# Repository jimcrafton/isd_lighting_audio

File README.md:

# isd_lighting_audio

Arduino nano code to control the audio and lighting effects for a Zvesda 1/2700 Star Destroyer model.

For WIP pictures of the model, see:
https://photos.app.goo.gl/XD3XtKHCLR6KuFhS9

Lighting effects based on NeoPixels, and custom code I wrote to activate them individually.

[Star Destroyer Start up Video, still WIP](https://photos.google.com/share/AF1QipOuW4K0J_yMDQOA_agWgGm0RNDhcW0MBYs12XNCtcLftvfbEZarzZgI_aQ6eU1jtA/photo/AF1QipNUU_HIZ2aDgCDPC5ougGlNus44bEYMES7hw9cd?key=Q3RFTWRxT3RHVC1FSkhQc0VzXzNoM1VPVWRwSmZR)

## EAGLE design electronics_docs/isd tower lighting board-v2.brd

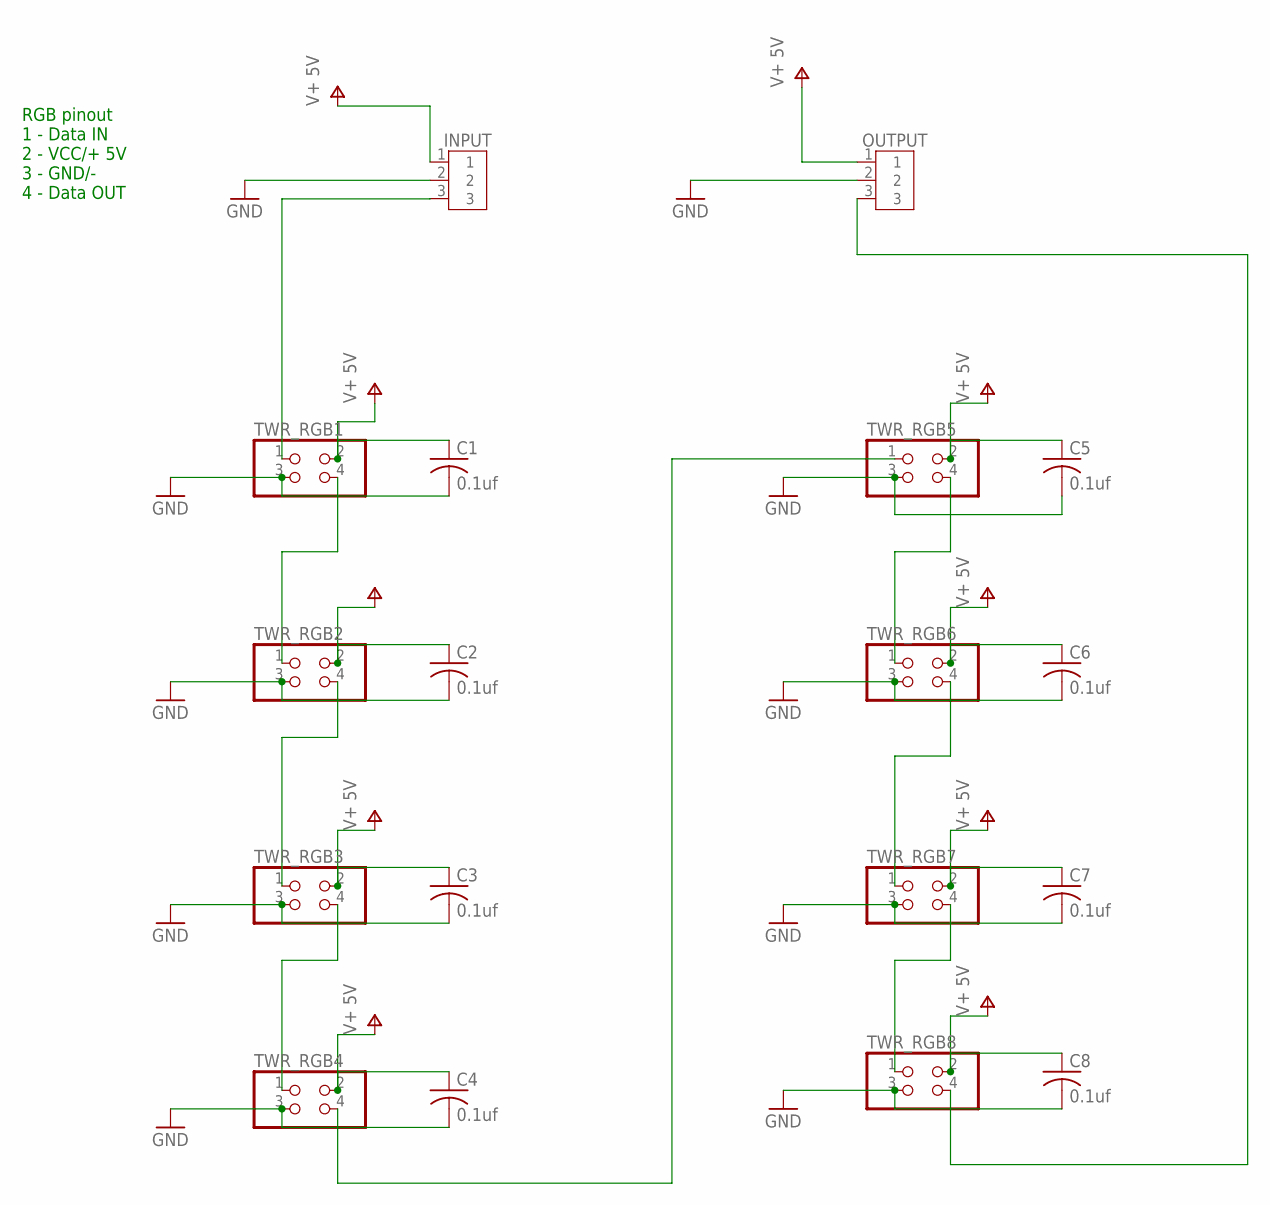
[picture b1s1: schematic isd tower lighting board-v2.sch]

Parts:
C1, C2, C3, C4, C5, C6, C7, C8: 0.1uf; C0805
INPUT: B3B-XH-A
OUTPUT: B3B-XH-A
TWR_RGB1, TWR_RGB2, TWR_RGB3, TWR_RGB4, TWR_RGB5, TWR_RGB6, TWR_RGB7, TWR_RGB8: PINHD-2X2; 2X02

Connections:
GND: C1.2, C2.2, C3.2, C4.2, C5.2, C6.2, C7.2, C8.2, INPUT.2, OUTPUT.2, TWR_RGB1.3, TWR_RGB2.3, TWR_RGB3.3, TWR_RGB4.3, TWR_RGB5.3, TWR_RGB6.3, TWR_RGB7.3, TWR_RGB8.3
unnamed: INPUT.3, TWR_RGB1.1
unnamed: TWR_RGB5.4, TWR_RGB6.1
unnamed: TWR_RGB6.4, TWR_RGB7.1
unnamed: TWR_RGB7.4, TWR_RGB8.1
unnamed: TWR_RGB4.4, TWR_RGB5.1
unnamed: TWR_RGB3.4, TWR_RGB4.1
unnamed: TWR_RGB2.4, TWR_RGB3.1
unnamed: TWR_RGB1.4, TWR_RGB2.1
unnamed: OUTPUT.3, TWR_RGB8.4
V+: C1.1, C2.1, C3.1, C4.1, C5.1, C6.1, C7.1, C8.1, INPUT.1, OUTPUT.1, TWR_RGB1.2, TWR_RGB2.2, TWR_RGB3.2, TWR_RGB4.2, TWR_RGB5.2, TWR_RGB6.2, TWR_RGB7.2, TWR_RGB8.2

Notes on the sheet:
RGB pinout 1 - Data IN 2 - VCC/+ 5V 3 - GND/- 4 - Data OUT

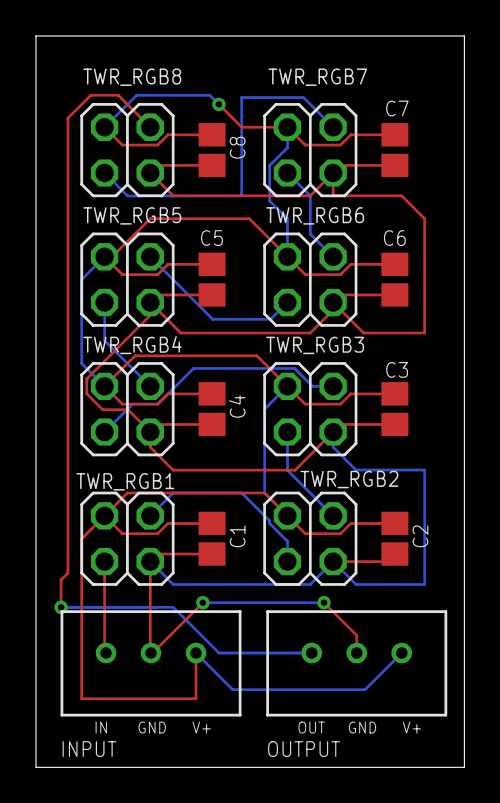
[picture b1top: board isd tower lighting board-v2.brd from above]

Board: 2 copper layers, 23.8 x 40.6 mm, 18 parts (0 on the bottom side), 11 nets.

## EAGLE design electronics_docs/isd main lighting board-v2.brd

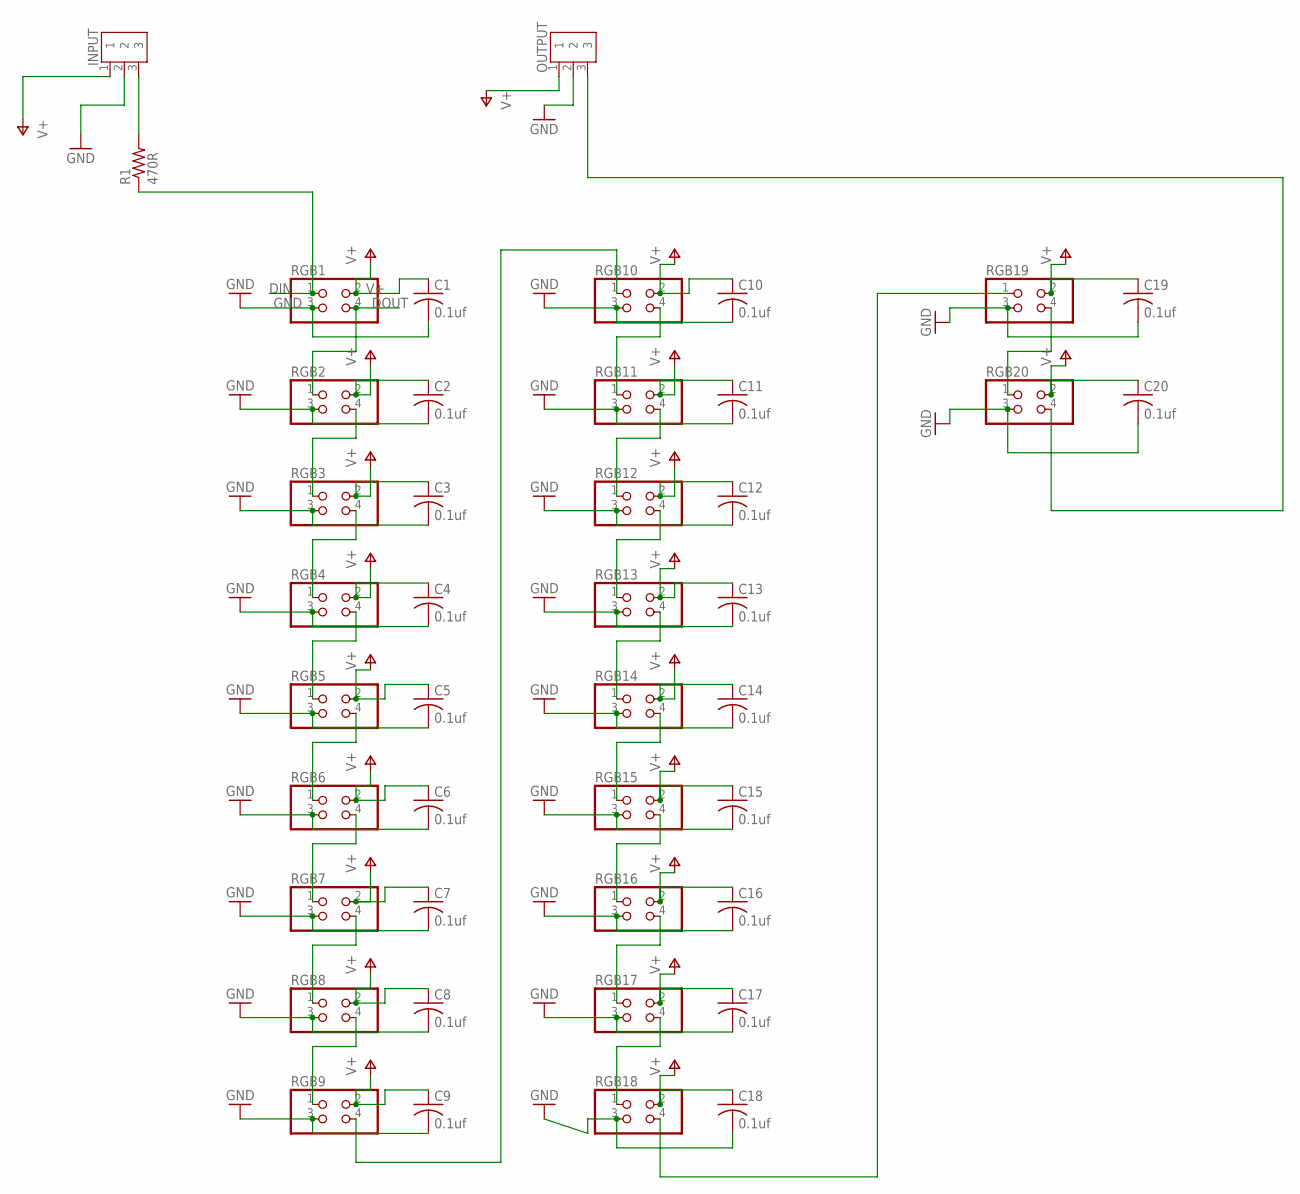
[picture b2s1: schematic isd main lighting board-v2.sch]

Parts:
C1, C2, C3, C4, C5, C6, C7, C8, C9, C10, C11, C12, C13, C14, C15, C16, C17, C18, C19, C20: 0.1uf; C0805
INPUT: B3B-XH-A
OUTPUT: B3B-XH-A
R1: 470R; 0204/5
RGB1, RGB2, RGB3, RGB4, RGB5, RGB6, RGB7, RGB8, RGB9, RGB10, RGB11, RGB12, RGB13, RGB14, RGB15, RGB16, RGB17, RGB18, RGB19, RGB20: PINHD-2X2; 2X02

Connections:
DIN: R1.1, RGB1.1
DOUT: RGB1.4, RGB2.1
GND: C1.2, C2.2, C3.2, C4.2, C5.2, C6.2, C7.2, C8.2, C9.2, C10.2, C11.2, C12.2, C13.2, C14.2, C15.2, C16.2, C17.2, C18.2, C19.2, C20.2, INPUT.2, OUTPUT.2, RGB1.3, RGB2.3, RGB3.3, RGB4.3, RGB5.3, RGB6.3, RGB7.3, RGB8.3, RGB9.3, RGB10.3, RGB11.3, RGB12.3, RGB13.3, RGB14.3, RGB15.3, RGB16.3, RGB17.3, RGB18.3, RGB19.3, RGB20.3
unnamed: INPUT.3, R1.2
unnamed: OUTPUT.3, RGB20.4
unnamed: RGB18.4, RGB19.1
unnamed: RGB8.4, RGB9.1
unnamed: RGB16.4, RGB17.1
unnamed: RGB19.4, RGB20.1
unnamed: RGB15.4, RGB16.1
unnamed: RGB14.4, RGB15.1
unnamed: RGB17.4, RGB18.1
unnamed: RGB13.4, RGB14.1
unnamed: RGB12.4, RGB13.1
unnamed: RGB11.4, RGB12.1
unnamed: RGB10.4, RGB11.1
unnamed: RGB9.4, RGB10.1
unnamed: RGB7.4, RGB8.1
unnamed: RGB6.4, RGB7.1
unnamed: RGB5.4, RGB6.1
unnamed: RGB4.4, RGB5.1
unnamed: RGB3.4, RGB4.1
unnamed: RGB2.4, RGB3.1
V+: C1.1, C2.1, C3.1, C4.1, C5.1, C6.1, C7.1, C8.1, C9.1, C10.1, C11.1, C12.1, C13.1, C14.1, C15.1, C16.1, C17.1, C18.1, C19.1, C20.1, INPUT.1, OUTPUT.1, RGB1.2, RGB2.2, RGB3.2, RGB4.2, RGB5.2, RGB6.2, RGB7.2, RGB8.2, RGB9.2, RGB10.2, RGB11.2, RGB12.2, RGB13.2, RGB14.2, RGB15.2, RGB16.2, RGB17.2, RGB18.2, RGB19.2, RGB20.2

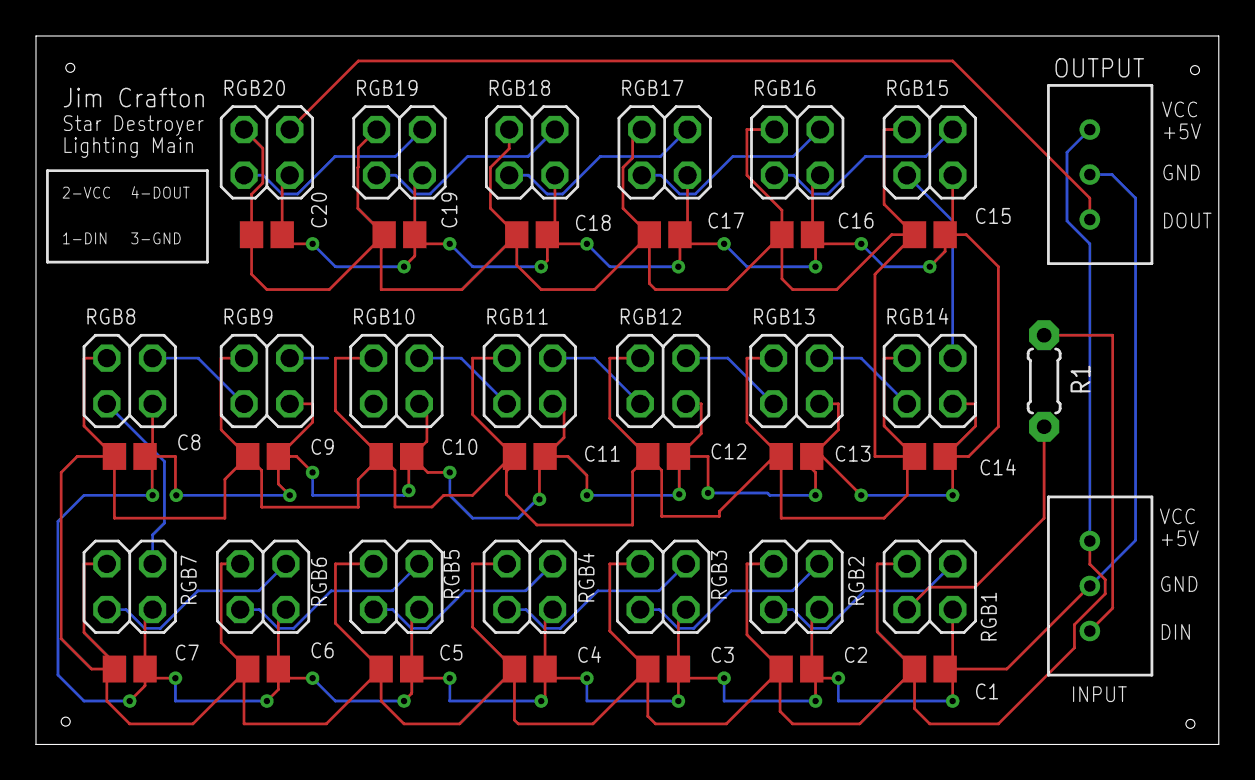
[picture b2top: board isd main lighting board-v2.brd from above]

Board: 2 copper layers, 65.7 x 39.4 mm, 43 parts (0 on the bottom side), 24 nets.

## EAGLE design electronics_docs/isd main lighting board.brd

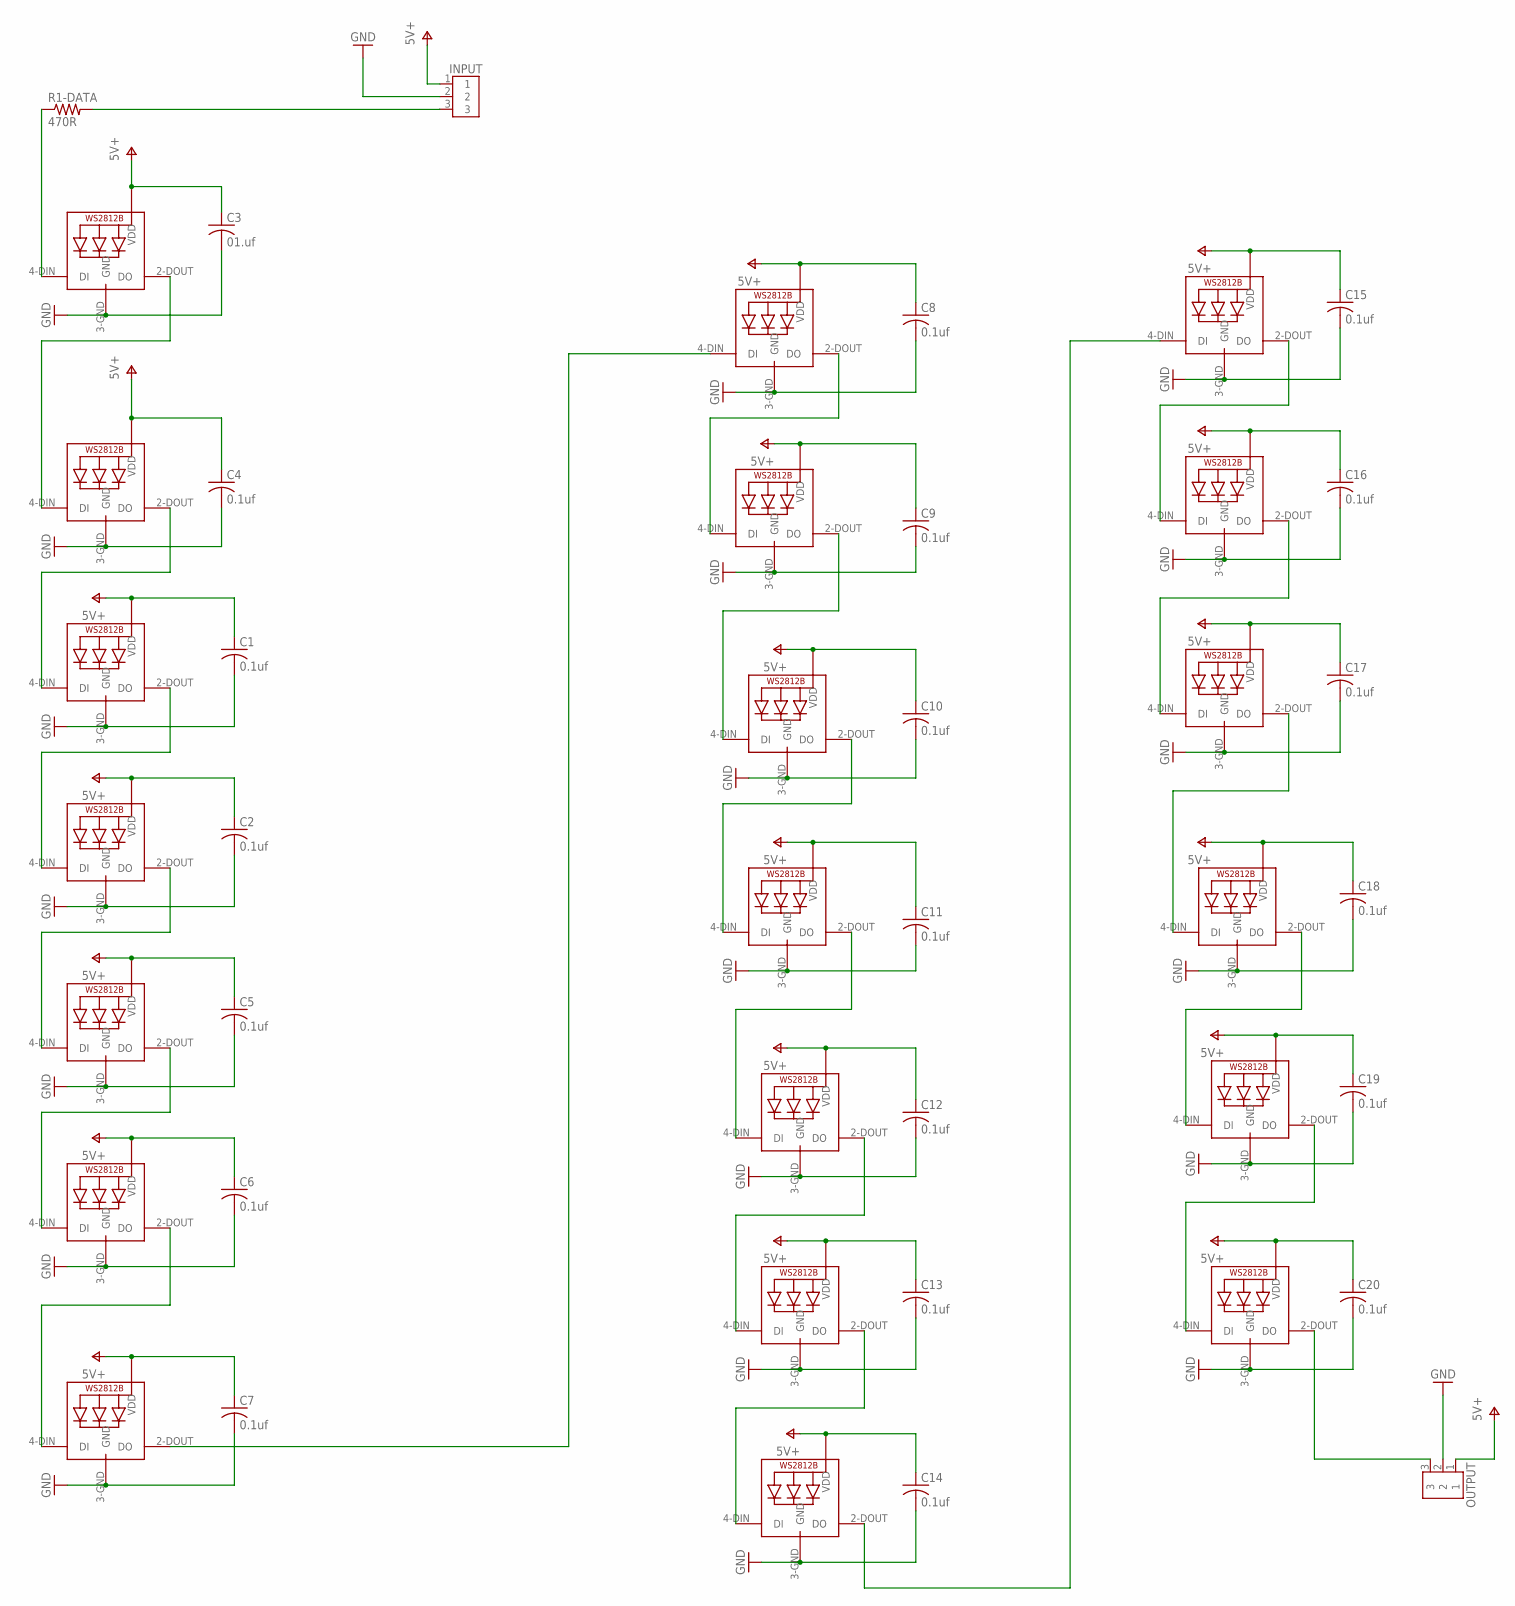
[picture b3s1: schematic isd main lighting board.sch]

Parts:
C1, C2, C4, C5, C6, C7, C8, C9, C10, C11, C12, C13, C14, C15, C16, C17, C18, C19, C20: 0.1uf; C0805K
C3: 01.uf; C0805K
INPUT: B3B-XH-A
OUTPUT: B3B-XH-A
R1-DATA: 470R; 0204/5
RGB1, RGB2, RGB3, RGB4, RGB5, RGB6, RGB7, RGB8, RGB9, RGB10, RGB11, RGB12, RGB13, RGB14, RGB15, RGB16, RGB17, RGB18, RGB19, RGB20: WS2812B_5050N; WS2812B-NARROW

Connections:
GND: C1.2, C2.2, C3.2, C4.2, C5.2, C6.2, C7.2, C8.2, C9.2, C10.2, C11.2, C12.2, C13.2, C14.2, C15.2, C16.2, C17.2, C18.2, C19.2, C20.2, INPUT.2, OUTPUT.2, RGB1.3-GND (GND), RGB2.3-GND (GND), RGB3.3-GND (GND), RGB4.3-GND (GND), RGB5.3-GND (GND), RGB6.3-GND (GND), RGB7.3-GND (GND), RGB8.3-GND (GND), RGB9.3-GND (GND), RGB10.3-GND (GND), RGB11.3-GND (GND), RGB12.3-GND (GND), RGB13.3-GND (GND), RGB14.3-GND (GND), RGB15.3-GND (GND), RGB16.3-GND (GND), RGB17.3-GND (GND), RGB18.3-GND (GND), RGB19.3-GND (GND), RGB20.3-GND (GND)
unnamed: R1-DATA.1, RGB1.4-DIN (DI)
unnamed: RGB1.2-DOUT (DO), RGB2.4-DIN (DI)
unnamed: RGB2.2-DOUT (DO), RGB3.4-DIN (DI)
unnamed: INPUT.3, R1-DATA.2
unnamed: RGB3.2-DOUT (DO), RGB4.4-DIN (DI)
unnamed: OUTPUT.3, RGB20.2-DOUT (DO)
unnamed: RGB4.2-DOUT (DO), RGB5.4-DIN (DI)
unnamed: RGB8.2-DOUT (DO), RGB9.4-DIN (DI)
unnamed: RGB5.2-DOUT (DO), RGB6.4-DIN (DI)
unnamed: RGB6.2-DOUT (DO), RGB7.4-DIN (DI)
unnamed: RGB7.2-DOUT (DO), RGB8.4-DIN (DI)
unnamed: RGB9.2-DOUT (DO), RGB10.4-DIN (DI)
unnamed: RGB10.2-DOUT (DO), RGB11.4-DIN (DI)
unnamed: RGB11.2-DOUT (DO), RGB12.4-DIN (DI)
unnamed: RGB12.2-DOUT (DO), RGB13.4-DIN (DI)
unnamed: RGB13.2-DOUT (DO), RGB14.4-DIN (DI)
unnamed: RGB14.2-DOUT (DO), RGB15.4-DIN (DI)
unnamed: RGB15.2-DOUT (DO), RGB16.4-DIN (DI)
unnamed: RGB16.2-DOUT (DO), RGB17.4-DIN (DI)
unnamed: RGB17.2-DOUT (DO), RGB18.4-DIN (DI)
unnamed: RGB18.2-DOUT (DO), RGB19.4-DIN (DI)
unnamed: RGB19.2-DOUT (DO), RGB20.4-DIN (DI)
V+: C1.1, C2.1, C3.1, C4.1, C5.1, C6.1, C7.1, C8.1, C9.1, C10.1, C11.1, C12.1, C13.1, C14.1, C15.1, C16.1, C17.1, C18.1, C19.1, C20.1, INPUT.1, OUTPUT.1, RGB1.1-VDD (VDD), RGB2.1-VDD (VDD), RGB3.1-VDD (VDD), RGB4.1-VDD (VDD), RGB5.1-VDD (VDD), RGB6.1-VDD (VDD), RGB7.1-VDD (VDD), RGB8.1-VDD (VDD), RGB9.1-VDD (VDD), RGB10.1-VDD (VDD), RGB11.1-VDD (VDD), RGB12.1-VDD (VDD), RGB13.1-VDD (VDD), RGB14.1-VDD (VDD), RGB15.1-VDD (VDD), RGB16.1-VDD (VDD), RGB17.1-VDD (VDD), RGB18.1-VDD (VDD), RGB19.1-VDD (VDD), RGB20.1-VDD (VDD)

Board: 2 copper layers, 43 parts (0 on the bottom side), 24 nets, no tracks yet.

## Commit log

2022-11-19 initial code for Imperial Star Destroyer model lighting and audio effect, controlled by Arduino and custom electronics
2022-11-21 renamed
2023-01-17 updated docs and code
2023-01-26 ISD bug fixes, had to get rid of primary and secondary audio controllers. now only one. bug fixes in BT controls.
2023-01-29 final fixes. got rid of dual audio handling, audio only processed on secondary MCU. Fixed up UI on mobile BT controller.
